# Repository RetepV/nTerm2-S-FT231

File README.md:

# nTerm2-S

> [!NOTE]
> This is the continuation of the design of the nTerm2-S (found here: https://github.com/RetepV/nTerm2-S). Now that I am reaching completion, I have decided to switch from using a CP2102 to using an FT231. The FT231 is just easier to solder with a soldering iron. Or better said: it CAN be soldered with a soldering iron, whereas with the CP2102 that's near impossible, it was a bad choice on my part.\
> \
> The version with the CP2102 will be 'archived', i.e. frozen. It really does work, you can build it if you like, it will run any FabGL code and example (except the MS-Dos emulator for lack of memory). But I will abandon it and continue developing on the FT231 version.

This is my rendition of the uTerm2-S by Just4Fun (https://hackaday.io/project/181583-uterm2-s-a-multi-emulation-color-rs232-terminal). My one is in SMD, and I hopefully made it easily hand-solderable for everyone. Obviously the 'n' in nTerm stands for 'nano.' :P

The nTerm2-S has a slightly more usable form than the uTerm2-S, I think. Smaller and more of a format of a useful tool. A "throw it in a drawer and grab it when you need it"- type of device. Taking little desk space and layed out for quick plugging and unplugging serial devices. For that I have also made it so that it can switch between normal and cross-cable (null-modem) from software, so that all you need is one cable and don't need extender boxes or a special null-modem cable.

It can also switch between hardware-supported RTS/CTS and DTR/DSR handshaking. With the sidenote that DTR/DSR are connected to RTS/CTS of the ESP32: the ESP32 does not have dedicated DSR/DTR signals in it's UART. It should work fine that way with old hardware, as the ESP32 is so fast that it will probably never have to deassert DTR (in reality RTS) anyway. And if the data set deasserts DSR, it means that the ESP32 will actually see CTS deasserted, and wait until CTS asserts again before continuing.

The nTerm2-S is ultimately based on the FABGL library and board design from Fabrizio Di Vittori. http://www.fabglib.org. However, I skipped Fabrizio's implementation and based my design on Just4Fun's uTerm2-S. https://j4f.info/uterm2-s

This board will run all FabGL software and examples, <ins>except</ins> the PC emulator. The PC emulator needs PSRAM, but the nTerm2-S does not have enough I/O pins left to connect a PSRAM. Maybe I will do a V2 at some point, using an I/O expander to free up ESP32 pins for connecting a PSRAM and an SD card. Or maybe I will make a new design using a newer version CPU. But let's finish the nTerm2-S first... ;)

# Software

For the software, please have a look here: https://github.com/RetepV/SporosTerm

All instructions for building the software from source are there. [But I also provide releases with handy scripts/batch files to easily program the board.](https://github.com/RetepV/SporosTerm/releases)

# Build instructions

I will provide build instructions here, when I actually have some. I'm going to build another one, and will make pictures.

# Progress

**27-2-2026**

Oops... I made a boo boo...

I have completely forgotten about the 5K1 resistors on the CC1 and CC2 lines of the USB-C connector. And hence, no USB-C device will provide power to the board, except some cheap and probably dangerous USB-C chargers. I knew I should have added them, I remember even making a mental note, but yet I never added them. How could this happen? Well, apart from simply my inexperience with USB, I have been testing all these months with a nice and long Nintendo USB cable, which has a USB-A on one end and a USB-C on the other. And I had it plugged into a USB hub, because I'd rather risk burning out the hub than a USB port on my laptop. But USB-A will happily provide power to anything, so my board always powered up fine. It was not until I wanted to change some settings in the FT231, and used a USB-C cable to directly connect it to my laptop, that I found the board didn't want to power up. Major facepalm. 🤦

Worst part (or better part, I'm not sure yet) is that this is quite a common mistake that people make. I should have know better, but on the other hand: it does make me feel a bit better that I'm not the only one. 😆

I quickly confirmed that this was the problem by wiring up the two resistors. And yep, now USB-C is giving the board power.

Adding two resistors seems like a quick and easy thing to do. But not this time, as the area where the resistors had to go was too crowded. So I had to refactor that whole area to make place. But now it looks a bit nicer too.

I also took the opportunity to update the graphics on the board. I moved some to the back and made them bigger (turns out that JLCPCB doesn't charge extra for solder mask on the back), added the URLs to these repositories, and add the FabGL and j4f repositories as well.

So here's v0.12. Only two resistors changed. Let's play a game of Spot the Differences:

This also has a consequence for the videos that I made. The videos are for a v0.11 board. What should I do? Make new boards yet again, and reshoot the videos? Maybe it's a good idea, because I learned a few things in the mean time, and the quality of the videos would become better. But the v0.11 videos are quite informational and educational already. I have to ponder this over a little.

By the way, I tallied up the costs of all the components. It comes down to about €40 for one board. But this was without looking for lower prices, I just went with the prices from Reichelt (https://www.reichelt.com).

[nTerm2-S FT231 BOM with prices.csv.zip](https://github.com/user-attachments/files/25616203/nTerm2-S.FT231.BOM.with.prices.csv.zip)

**26-2-2026**

I have been making videos while going from this:

To this:

I now have some video editing to do, which I have never done before in my life. Including adding a voiceover, because most of the time I was silent and concentrated during soldering. I did talk to myself in a few places, maybe I'll keep that. :)

A few mistakes were made, and I will show them uncensored. It resulted in a bunch of tips that are of general use when handsoldering SMD components. Let's see if I can make it educational. I hope that it will help some people take the plunge into SMD soldering. It's really not that hard. Just that you might need a 5x or 10x magnifying glass, like I do.

This is my fourth board (the other three were prototypes), and I was able to make it work in one go. When you watch the video, you'll see that I had a bit of jittery fingers, and that it caused me to make some mistakes. No shame in that!

**16-2-2026**

Just mentioning some progress here. I have started to build a new nTerm2-S, and am recording that. I have the handicap of not having great eyes anymore and have to solder using a magnifying glass these days. And this gets in the way of filming. So I had to rig something together. In the end I was able to ty my iPhone to the magnifying glass in such a way that I could look past it, while the iPhone looked straight down at my work area and my hands. That actually worked much better than I thought, except that if I accidentally touch the magnifying glass, the video wobbles a bit. :) Let's see if I can edit that out. No tricks, just honest handsoldering, including jittery hands, accidental baking of a resistor, and the occasional mistake that needed to be redone.

Anyway, here's a little unedited preview. Click it to play in Youtube.

**3-12-2025**

I found a little time to finally finish v0.11. This is it. I am not going to add anything more. Done deal. I will ask JLCPCB to fabricate a new set of v0.11 boards and will then build up one for the purpose of making pictures on how to solder one together. Maybe I'll make a video, which will be my first.

At the last possible moment, I added a 3-terminal pin header to optionally attach a 10K potmeter to, to use as volume control. I realised a bit late that if you build the amplifier and connect a speaker directly to the board, there is no way to control the volume. I can add volume control in software, but really: if you accidentally have the volume booming too loud, would you rather want to turn a volume pot or go into the setup menu, choose 'Audio', decrease the volume, and press Save? Anyway, it is optional and you can leave it out. Just don't forget to connect pins 1 and 2 on the 3-pin VOLUME header and solder R19. All info in the schematic.

I also improved some routing, and a few other little things.

**2-11-2025**

I have the Bluetooth working more or less great with Linux. I can pair, connect, disconnect, connect, disconnect, et

The problem of Macos, not properly being able to reconnect after a disconnect, seems to be a bug of Macos specifically. The Serial Port Profile (SPP) support on Macos is buggy. I have reported the bug with Apple, let's see wat happens.

**1-11-2025**

In between wrestling with trying to get the Bluetooth Serial Port Profile working and stable (which I am only moderately successful in, to be honest), I spent some time on a useless but fun thing: a signon screen. :)

About the Bluetooth SPP. It seems that I have it mostly under control now, it's quite usable and I'm not missing characters anymore. However, there is a problem that after pairing, it's only possible to connect one time. If we disconnect and try to connect again, the connection seems to be made, but no data is being transferred. If the nTerm2-S is 'forgotton' and paired again, it will work again for one connection only.

After browsing the internet, it seems that I am not the only one with this issue, and that it looks to be an issue with the ESP32's Bluetooth implementation loosing the pairing key for some reason.

There are some questions on the Espressif forums, and this one is quite detailed and seems to explain the issue quite well: https://esp32.com/viewtopic.php?p=151510&hilit=esp32+spp#p151510

**26-10-2025**

That newt had it coming, I swear!

@Fabrizio: it's really working well. Great job, thank you for all the work you did!

**26-10-2025**

I have been working on the software, and on testing. I don't have access to all types of hardware, but for now I have been testing with these:

* A Synertek SYM-1, which is the oldest computer that I currently own.
* An old(ish) Macbook (i7) running Ubuntu 24.04, with a serial dongle that is RS-232 V.24, i.e. uses -12V/+12V for communication.
* The latest version of the nTerm2-S, but without the audio and relay circuits (minimum configuration).
* A previous version of the nTerm2-S that I fully built for prototyping, and does have the audio and relay circuits.

I have been testing at different baud rates, and have been able to go all the way down to 110 baud successfully.

The SYM-1 doesn't go lower, so I thought to use my Linux machine to try `agetty` at 50 baud. But for some reason nothing under 110 baud would work. However, when I connect two nTerm2-S devices together, they can perfectly well communicate at 50 baud. So I suspect that the serial USB dongle has an issue with anything below 110 baud. I will have to check the signals with a scope to see what's really going on. The USB dongle uses a PL-2303 chip, and according to the datasheet it should be able to go down to at least 75 baud, and I suspect even lower. Maybe it's a driver issue.

On this latest prototype of the nTerm2-S, I did not populate the relay circuits. So to connect it to the Linux machine, I had to dig up a bunch of converters. And I had to quickly wire a null-modem converter too. So this reminded me again of why I added those relay circuits. They are worth it. :)

It IS actually a weird feeling to communicate with such a powerful Macbook over 110 baud. It really gave me the feeling that I was calling remotely into an old timesharing mainframe computer. :P

While testing with `agetty`, I found that I had forgotten to implement BRK functionality. So I quickly added that, and now I can ask `agetty` to cycle through a bunch of predetermined baud rates to match my nTerm2-S's baud rate.

Here's a picture of two nTerm2-S's connected to each other, where one has the relay circuits. No huge tree of converters, just one converter to go from DB25 to DB9, and then just set the Modem Type to 'Null modem' in the settings!

Another thing is the supported display resolution and display modes... Currently I offer 2 resolutions: 640x350 and 800x480. 800x480 is closest to the DEC VT340, which apparently was 800x500 pixels. At 800x480, there is just enough memory to have 8 colors (4 low and 4 high intensity). But it does give high resolution graphics, and it also gives a quite readable 132x25/50 characters (6 pixels wide characters).

At 640x350, I can have 16 colors. But what's more is, that if I use 640x350 monochrome, I can have the Bluetooth stack running! So it looks like I will support the following modes:

* 640x350, [80x24 + status bar, 80x25, 80x48 + status bar, 80x50], 2 colors, bluetooth
* 640x350, [80x24 + status bar, 80x25, 80x48 + status bar, 80x50], 16 colors, no bluetooth
* 800x480, [80x24 + status bar, 80x25, 80x48 + status bar, 80x50, 132x24 + status bar, 132x25, 132x48 + status bar, 132x50], 8 colors, no bluetooth

I do have a font that tries to show something readable when using 132x25 characters on a 640x350 resolution screen. It's not really something I take serious, but the font is there and is added quickly enough. Maybe it's worth it for some edge cases. Or just maybe, I could get a resolution of 800x350?

Higher resolutions than 800x480 are possible, but simply mean less colors because the ESP32 just does not have enough memory. There seems to be a solution for that, by adding PSRAM. But that would mean a hardware redesign, because there are no pins left to connect a PSRAM. I would have to add an I/O expander, either i2c or maybe 1-wire. That will only happen in a possible next version, which I will then probably also base on an ESP32-S3 (because it can do both UART and JTAG over USB, and is therefore tremendously much easier to debug).

I actually made a proof of concept already beginning of this year. But I will not build it (and it's not finished), as I really want to move on to the ESP32-S3 or maybe even something better.

https://github.com/RetepV/nTerm2-S-SD

**25-10-2025**

The last update was quite some time ago. I have been struggling with both time to work on this project, and struggling with the rendering issue of the terminal application. Somehow the glyph options of the Status Bar would sometimes 'bleed' over to the terminal text, causing letters to appear in reverse video. I had an inkling that this was being caused by the Status Bar rendering being interrupted by serial data being received and also rendered to the screen. Serial data is being received on an interrupt basis, so this was happening. However, I did not understand why.

It turns out that when we want to render a glyph on the Canvas, we use a function `drawText()`. But the glyph options (and foreground and background colors) are not passed together with the text. Instead, we use `setGlyphOptions`, `setPenColor` and `setBrushColor` to set up the parameters, and then call `drawText`, which will use the parameters that we set up. What the Canvas actually does with these calls is to post a message into a queue that will be read and processed by the DisplayController. This is necessary because the Canvas and the DisplayController code run on different cores and we need to take care of synchronising the messages: we cannot interrupt the DisplayController when we want, because that will lead to visible screen glitches. Using a queue is probably the easiest way to do this.

However, **both** the Canvas and the DisplayController keep their own version of those settings, i.e. there is more than one source of truth. The sources of truth are not updated at the same time, and that means that there is always a small amount of time where both will be out of sync. And this is the reason why sometimes the text received from the RS-232 was rendered with the `glyphOptions` of the Status Bar.

This is actually not so hard to fix. We just need to have only one source of truth, and pass the parameters together with the other relevant data (Glyph) through the queue. However, that would be a major fix, and actually a paradigm change. It could potentially have a lot of side effects, and I am not yet feeling up to handle that. Besides, it would be a backwards-compatibility breaking fix and so cannot be pushed back into Fabio's FabGL branch. And as I am only interested in the terminal emulation, I think I would better trip the FabGL library of all that is unnecessary and make a FabGLTerm or FabGLLite version or something. And I'm not sure if that is allowed by the license.

Anyway, another way to go is to leave everything as it is and simply **add** a `drawGlyph` command that takes `glyphOptions`, `penColor` and `brushColor`, and renders the glyph with the passed parameters instead of the (doubly) stored global `glyphOptions`, `penColor` and `brushColor`, call it `drawGlyphWithOptions`, and use that call to render the Status Bar. No sooner said than done, and the glitches disappeared. Success!

All the time that I was trying to work this out, I was wishing that I could connect a debugger to trace what was going on. But all the GPIO pins on the ESP32 are used for something, and there are no free pins to connect a JTAG debugger. This makes everything really hard to debug. If I make a next version of the nTerm2-S, I will choose for the ESP32 S3, which can do serial communications **and** JTAG over its USB port, making life so much easier.

Next steps are to clean up everything, reorganize the repository a bit, test with many more devices, and write some documentation. Possibly add a feature or two more.

What I have not mentioned before, is that I have also been busy implementing Bluetooth serial communications. The idea is that you can connect your PC to the Bluetooth UART and monitor what happens on the nTerm2-S. And more: you can send keystrokes to the nTerm2-S, which will forward it to the connected serial devices. The nTerm2-S is basically proxying between the serial device and the PC. The best part of this is that not only can you record the received serial data on the PC, but can also send data to the serial device, meaning that you can use the nTerm2-S to upload data. There are a few things to still iron out, but it's coming along quite nicely.

**23-6-2025**

Fixed a few small layout issues that I encountered while soldering, and then submitted as V0.10.

- Fixed orientation of C19.
- Changed orientations of R19 and C3. If you don't want the audio amplifier, you will still have to solder in the filter components R20, R21, C7 and C3. I placed C3 right under C7 now, and R19 (which does not need to be added) below that, making it more obvious what needs to be soldered and what not.
- Somehow the designation of C3 disappeared, I brought it back.
- Tweaked the positions of the connectors so that they are flush with the PCB edge. I should have done that earlier.
- Connected pins 2 and 3 of the CR2032 battery holder together. I didn't have the correct battery holder, so I soldered one in with a wire. I had to solder to pin 1 (-) and 3 (+) of the battery holder. But looking at the PCB, pin 2 is unconnected but also shows '+' in the solder mask. That's confusing, so I connected pin 2 to pin 3 so now both + pins can be used.

Here's the final result of v0.09. This is without the previously mentioned fixes, zoom in on the picture to find the issues. ;) 

I thought it might be nice to show the equipment that I use to solder nTerm2-S. This is it. Nothing more (ok, I also wear reading glasses).

- A lamp with 2x magnifying glass
- A small 10x magnifying loupe
- A steel set of quality pincers
- Edsyn FL-22 flux
- A Pinecil DC5525 soldering iron with ST-BC2 tip (the short variant of the BC2)
- 0.5mm 60/40 rosin-core solder
- A Goobay silicone soldering mat
- Forgot to picture: [a benchtop solder fume extractor](https://www.reichelt.com/nl/nl/shop/product/soldeerdamp-filtersysteem_zd-153_1m_min-90929?PROVID=2809&gad_source=1&gad_campaignid=22421704484&gclid=CjwKCAjw9uPCBhATEiwABHN9KxTfvpmQ8-ziKVJnDUi2Y7wfs4gk6s1T8yYnybVX92MnH0qx3_6JcRoCZEIQAvD_BwE), the most basic type

I also have a hot air station. But one of my goals is to make the nTerm2-S solderable without hot air, so I don't use it (I did need it for the CP2102, which is why I dropped that chip). I find that using hot air is not faster than hand soldering, possibly even slower. Hot air does have the benefit, though, that the components will align themselves automatically. The fastest way, however, will be to use solder paste with a stencil, and bake the PCB in an SMD oven. I don't have one, so hand soldering it is. ;)

And then software. Software is coming along quite well, but I have to iron out one quite major thing. The FabGL 'canvas' class works great if you only have one source of data. But I need to render the terminal text from serial input, but also the bottom status bar, so the canvas has 2 sources of data. Canvas, however, only has one set of text properties (bold, inverse, etc.). The serial input and status bar are sharing the text properties, and so I get some random inverse letters in the terminal text, when serial data is received while I'm in the middle of rendering the status bar. I really don't want to change FabGL much, but this is a fundamental problem of Canvas. It has only one render queue, and text properties are global to Canvas and are not properties of the drawText commands that are being put in the queue. There are some different options, but all seem hacky, and I have already kind of hacked the status bar into FabGL as it currently is. I might have to take a step back and change the strategy.

**22-6-2025**

Soldered the minimum configuration of the board for working as a SporosTerm, which means: everything except the relays and their control, and the audo amplifier. Technically, the LEDs and the RTC are not necessary either, but I consider them an indispensible part of the terminal. PCB is not cleaned of flux yet, so it looks dirty.

Connected everything and fired it up, and everything works. FabGL's Space Invaders, AnsiTerminal, Altair 8800 work. And SporosTerm works super too. The RTC works, it kept its time overnight. 

**21-6-2025**

Soldered R39 and R40, and the FT231 is recognized. The USB wants to give us 500mA, and on-board we have a perfect 3V3. The protection diodes work fine too.

Let's solder the ESP32, the reset circuitry and the power led. Then we can test if the ESP32 can be flashed.

Yep. Flashing works.

**20-6-2025**

Soldering commences, the FT231 solders really easily, that's a success! I did find one sloppyness on my side, C19 is rotated the wrong way. Of course it works just as fine in this orientation, but for sure people will accidentally solder it in the wrong way, as all the other C's are oriented the other way. That needs to be fixed in a V0.10, but it's cosmetic so no risk of breaking something.

Then life came in the way before I was able to solder R39 and R40, so I can't test yet.

**18-6-2025**

Received the new PCBs today. Won't be able to solder them as yet, other things have priority. :)

**12-6-2025**

I actually ordered 5 new boards from JLCPCB on 5-6-2025 (€15,99 including shipping). They were finished and shipped on 7-6-2025. Arrived in Leipzig (Germany) on 8-6-2025. They are taking their time and still have the package in their posession on 12-6-2025. So now waiting for them to pass it over to The Netherlands so that it can be delivered to me. What I learn from this is that the Chinese are very efficient, while the Germans seem to have lost their knack. I guess I shouldn't expect anything until end of next week.

Just before sending the board for manufacturing, I decided to add a few more solder bridges.

OPT1: Option to choose between using the on-board audi amplifier, or leave it out completely and have line-out.
OPT2-OPT5: Option to choose between having the null-modem switching option or not. If you don't want to use the null-modem option, you can leave out the relais and their control circuitry, and use the OPT2-OPT5 solder bridges to connect the UART directly to the RS-232 V24 connector. Note that this also removes the capability to switch between RTS/CTS and DTR/DSR.

So if you want to save a bit of money and don't want to use those subcomponents, you now can solder the bridges accordingly, instead of using a bypass bodge wire.

Ah, I also found out that the footprint for the VGA connector had been wrong all along. With both the prototypes, it was kind of hard to put the VGA connector pins in their holes. It turned out that the spacing was wrong. The connector would fit with a little bit of pushing, but that's not right. So I updated the footprint, and it should be good now.

**5-6-2025**

Three things progressed.

1. I decided to drop the supercap. I don't think it will last so long, they are meant to bridge short power downs, not long ones. I tested with a CR2032 and a BAT43 diode, and that works just as reliable as battery backup, but will give waaaaay more backup life.
2. I decided to add OPT2...OPT5 solder bridges to give people the options of leaving out the resistors and driver circuits. Soldering 1-2 on the solder bridges will make the signals go through the relay circuits, i.e. have software switchable RxD/TxD, RTS/CTS, or DTR/DSR. Soldering 2-3 will connect RxD, TxD, RTS and CTS directly to the RS-232 connector. It can save you some money if you don't need the switchability, and you can always change your mind later.
3. I also decided that This Is It. No more features, no more nothing, nTerm2-S is feature complete, and I am going to order new PCBs to see if everything actually still works. If everything works as planned, then I will consider nTerm2-S as being released. Software is hard on it's way. But if you can't wait, you can already use FabGL's AnsiTerminal example: the nTerm2-S hardware is backwards compatible.

The scary part is the FT-231 circuit. I have not tested it, and have to hope that I didn't make a mistake. The other more or less scary thing is that I had to move the AUDIO_PWM track, and hope that I did not introduce a bunch of crossover. The AUDIO_PWM track had to cross over the RxD_0 and TxD_0 lines. But these are only used for the ESP32 console ouput or during updating of the firmware. So if console output is removed, there should simply be nothing to cross over.

**29-5-2025**

The real time clock survived the night on only the backup power. :) At the last moment, I decided to put a series resistor of 150 ohm with the supercap (there was none in [Dallas's reference design](https://nl.mouser.com/datasheet/2/272/rtc-4-click-manual-v100-1483841.pdf). The inrush current when the supercap is empty of charge could be quite high. It's just for a short time, but theoretically it could cause such a power dip that it would cause boot loops. I haven't measured the inrush current, but "the word" is that it could even be multiple Amperes, which could theoretically also cause a track to burn.

I used a used Panasonic 1F 5.5V supercap that I had lying around, while I waiting for new ones to arrive.

I will also do some experiments with using a battery and an extra BAT43 diode. That's also 2 components, and maybe a better plan. If the voltage drop over the diode is too high, maybe I could use a NID5100?

**28-5-2025**

I just wanted to share some images of the progress I am making. I am still using the previous board with the CP2102 for developing and prototyping.

This is my development set up. I am testing with an actual computer, a Synertek SYM-1. It has 8K of ram, and runs Microsoft BASIC. Also note the tiny screen that I'm using. It's an old 800x480 LCD screen that I had laying around. I found out that it was LVDS, and purchased a board that can convert VGA (and HDMI and CVBS) to LVDS to drive the screen. Next thing is to make a case for it, but I couldn't wait to use it.

Closeup of the nTerm2-S and the screen.

Here I have added the DS2417 real time clock. It was easy, thanks to a whole bunch of people who created the [Arduino OneWire library](https://www.pjrc.com/teensy/td_libs_OneWire.html). I'm using a supercap as backup solution now, but might maybe switch to using a CR2023. But I'm not sure if that will work. I would have to add another diode in series making the voltage (in theory) 3V - 0.4V = 2.6V. But the lowest voltage supported by the DS2417 is 2.5V, so it's right on the edge. With the supercap I have some 3.2V. But the supercap will maybe last 2 weeks or so, while the CR2023 would probably last for years.

**23-5-2025**

What makes the difference between a home computer and a professional computer? The Real Time Clock! While working on the nTerm2-S firmware, I was able to add a status bar to the terminal. Memory is really tight, but CPU performance is not. So I thought: let's update it 10 times a second and show some sort of status of Rx, Tx, RTS and CTS, some blinkenlights. And then I thought that it would also be nice to show the time (and maybe date) in the status bar. That was quickly added. But well, what good are the time and date if you need to enter it manually every time you reset the terminal. So, we need an RTC.

Looking at the GPIO's left on the ESP32, there was a problem. Only one bidirectional GPIO (14) and one input-only (36) left. What can we do with that? I2C is out of the question, we need 1 output (or bidirectional) and 1 bidirectional GPIO for that. SPI even needs 3 GPIOs, and might possibly be done with only 2. But we have only 1 bidirectional wire... 1-wire! And looking around, I found the [Dallas Semiconductor DS2417](https://www.analog.com/media/en/technical-documentation/data-sheets/ds2417.pdf).

The DS2417 is not truly a real-time clock, but rather a 64-bit counter that is auto-incremented once a second, i.e. a timestamp. This is fine, in firmware we can convert it to a proper date and time with some functions. The counter can be battery backed-up. Perfect enough for a real-time clock. I will power it from a supercap, like in Dallas's design. Hopefully it will hold a charge for many months. If not, I might have to change the design again, to use a normal battery with a diode. First I'll build it on a breadboard to test it out somewhat.

The chip also has a kind of alarm function. Basically we can program it to give a /INT pulse after 1, 4, 32, 64, 2048, 4096, 65536, or 131072 seconds. Not of too much use, but as we also have one input-only GPIO left, we can connect the INT to it. Fortunately the input-only GPIO is GPIO14, which is one of the so-called RTC-GPIO and can be used to wake up the ESP32 from deep sleep. I don't have any idea for what we could use it. But it fills up the last unused GPIO pin, and it's a fitting for a complete feature-freeze and release of the hardware.

So said, so done (Dutch proverb). It was a bit of a tight squeeze because of the supercap battery's size. And I have always tried to make sure that the AUDIO_PWM is not close to any of the high-speed signals to prevent crosstalk (which would be hearable in the audio), so I had to lay that out differently as well. Hopefully crosstalk from the video into the audio track will still be next-to-nonexistent.

So now we are here:

# License

THIS IS A WORK IN PROGESS! I.E. UNLESS STATED AS WORKING, ASSUME THAT IT DOES NOT WORK! (but it's looking real good ;))

This design is available under GPL License V3. This means that I DO NOT release it for commercial use, unless with my explicit written and signed consent. Please contact me first if you have commercial questions.

uTerm2-S: https://hackaday.io/project/181583-uterm2-s-a-multi-emulation-color-rs232-terminal  
fabgl: http://www.fabglib.org/, https://github.com/fdivitto/FabGL

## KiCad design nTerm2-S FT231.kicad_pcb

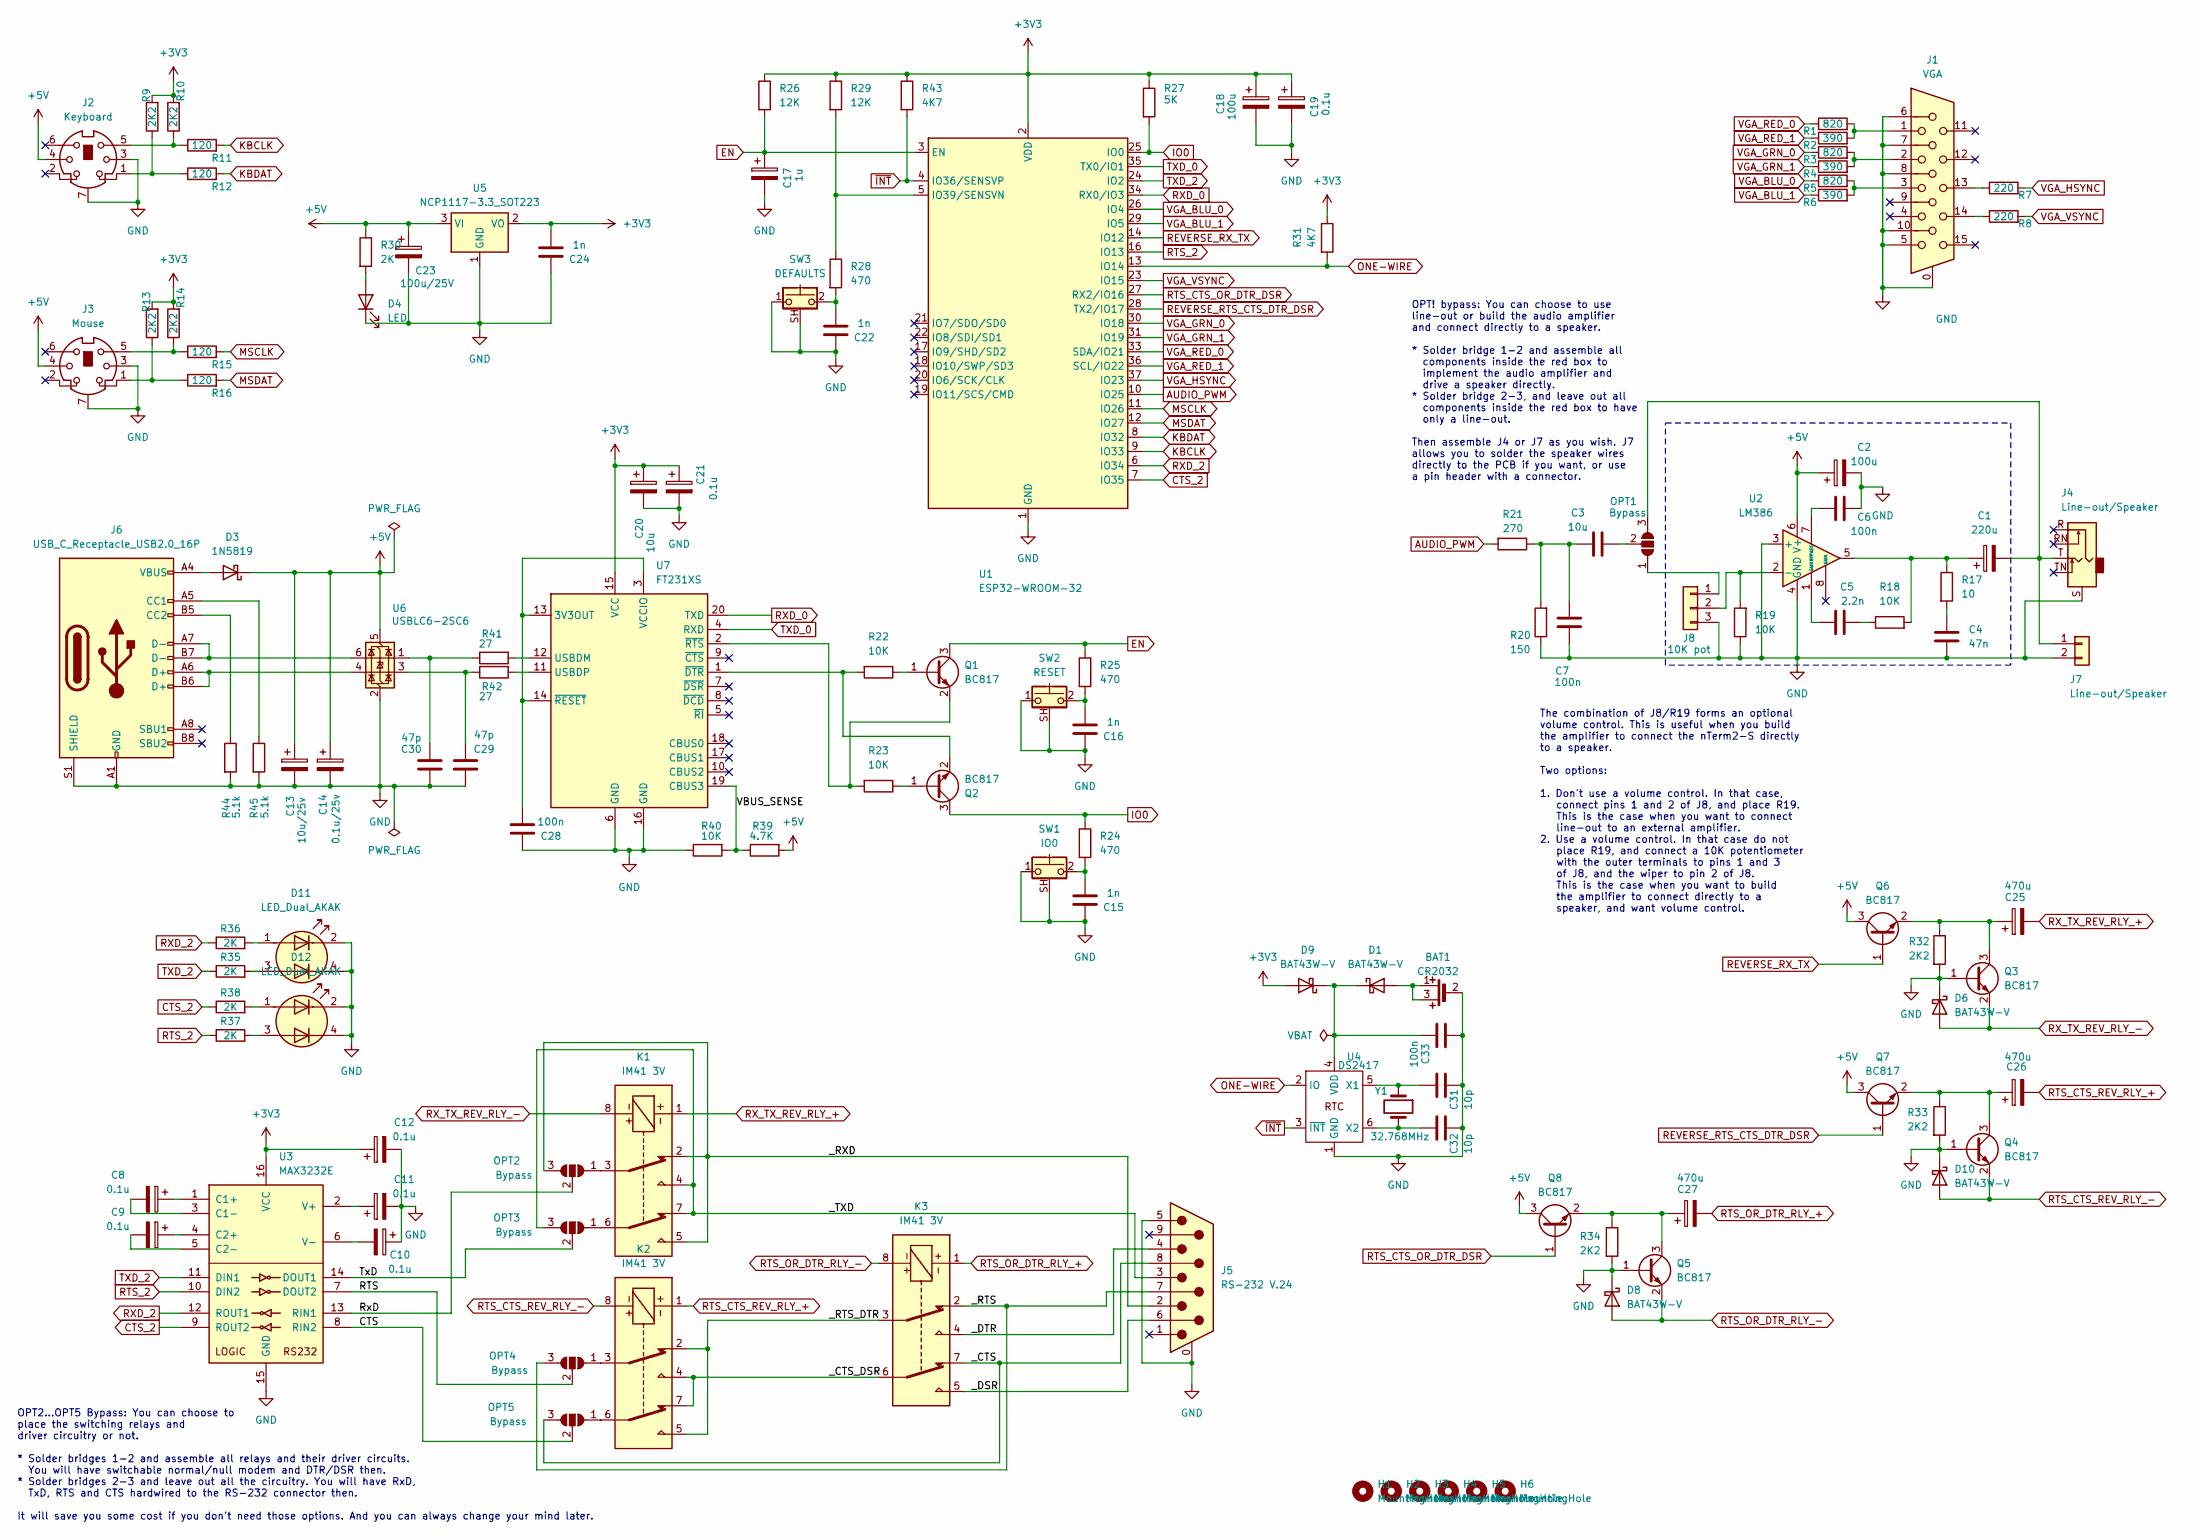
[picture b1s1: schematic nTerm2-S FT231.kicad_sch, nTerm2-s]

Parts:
BAT1: CR2032; TE Connectivity CR2032 V
C1: 220u; CP_Elec_6.3x7.7
C2: 100u; CP_Elec_5x5.4
C3: 10u; C_0805_2012Metric_Pad1.18x1.45mm_HandSolder
C4: 47n; C_0603_1608Metric_Pad1.08x0.95mm_HandSolder
C5: 2.2n; C_0603_1608Metric_Pad1.08x0.95mm_HandSolder
C6, C7, C28, C33: 100n; C_0603_1608Metric_Pad1.08x0.95mm_HandSolder
C8, C9, C10, C11, C12, C19, C21: 0.1u; CP_EIA-3216-18_Kemet-A_Pad1.58x1.35mm_HandSolder
C13: 10u/25v; CP_EIA-6032-28_Kemet-C_Pad2.25x2.35mm_HandSolder
C14: 0.1u/25v; CP_EIA-3216-18_Kemet-A_Pad1.58x1.35mm_HandSolder
C15, C16, C22, C24: 1n; C_0603_1608Metric_Pad1.08x0.95mm_HandSolder
C17: 1u; CP_EIA-3216-18_Kemet-A_Pad1.58x1.35mm_HandSolder
C18: 100u; CP_EIA-6032-28_Kemet-C_Pad2.25x2.35mm_HandSolder
C20: 10u; CP_EIA-3528-21_Kemet-B_Pad1.50x2.35mm_HandSolder
C23: 100u/25V; CP_EIA-7343-30_AVX-N_Pad2.25x2.55mm_HandSolder
C25, C26, C27: 470u; CP_Elec_6.3x7.7
C29, C30: 47p; C_0603_1608Metric_Pad1.08x0.95mm_HandSolder
C31, C32: 10p; C_0603_1608Metric_Pad1.08x0.95mm_HandSolder
D1, D6, D8, D9, D10: BAT43W-V; D_SOD-123
D3: 1N5819; Nexperia_CFP3_SOD-123W
D4: LED; DIALIGHT_LED_3MM_SINGLE
D11, D12: LED_Dual_AKAK; DIALIGHT_LED_3MM_DOUBLE
H1, H2, H3, H4, H5, H6: MountingHole; MountingHole_3.2mm_M3
J1: VGA; DSUB-15-HD AssMann HD 15FW
J2: Keyboard; Connector_Mini-DIN_Female_6Pin_2rows
J3: Mouse; Connector_Mini-DIN_Female_6Pin_2rows
J4: Line-out/Speaker; Jack_3.5mm_Ledino_KB3SPRS_Horizontal-alt
J5: RS-232 V.24; DSUB-9_Pins_Horizontal_P2.77x2.84mm_EdgePinOffset7.70mm_Hou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
J6: USB_C_Receptacle_USB2.0_16P; USB_C_Receptacle_Molex_213716-0001
J7: Line-out/Speaker; PinHeader_1x02_P2.54mm_Vertical
J8: 10K pot; PinHeader_1x03_P2.54mm_Vertical
K1, K2, K3: IM41 3V; Relay_DPDT_AXICOM_IMSeries_Gullwing
OPT1, OPT2, OPT3, OPT4, OPT5: Bypass; SolderJumper-3_P1.3mm_Open_RoundedPad1.0x1.5mm_NumberLabels
Q1, Q2, Q3, Q4, Q5, Q6, Q7, Q8: BC817; SOT-23
R1, R3, R5: 820; R_0603_1608Metric_Pad0.98x0.95mm_HandSolder
R2, R4, R6: 390; R_0603_1608Metric_Pad0.98x0.95mm_HandSolder
R7, R8: 220; R_0603_1608Metric_Pad0.98x0.95mm_HandSolder
R9, R10, R13, R14, R32, R33, R34: 2K2; R_0603_1608Metric_Pad0.98x0.95mm_HandSolder
R11, R12, R15, R16: 120; R_0603_1608Metric_Pad0.98x0.95mm_HandSolder
R17: 10; R_0603_1608Metric_Pad0.98x0.95mm_HandSolder
R18, R19, R22, R23, R40: 10K; R_0603_1608Metric_Pad0.98x0.95mm_HandSolder
R20: 150; R_0603_1608Metric_Pad0.98x0.95mm_HandSolder
R21: 270; R_0603_1608Metric_Pad0.98x0.95mm_HandSolder
R24, R25, R28: 470; R_0603_1608Metric_Pad0.98x0.95mm_HandSolder
R26, R29: 12K; R_0603_1608Metric_Pad0.98x0.95mm_HandSolder
R27: 5K; R_0603_1608Metric_Pad0.98x0.95mm_HandSolder
R30, R35, R36, R37, R38: 2K; R_0603_1608Metric_Pad0.98x0.95mm_HandSolder
R31, R43: 4K7; R_0603_1608Metric_Pad0.98x0.95mm_HandSolder
R39: 4.7K; R_0603_1608Metric_Pad0.98x0.95mm_HandSolder
R41, R42: 27; R_0603_1608Metric_Pad0.98x0.95mm_HandSolder
R44, R45: 5.1k; R_0603_1608Metric_Pad0.98x0.95mm_HandSolder
SW1: IO0; SW_Tactile_SPST_Angled_PTS645Vx58-2LFS-alt
SW2: RESET; SW_Tactile_SPST_Angled_PTS645Vx58-2LFS-alt
SW3: DEFAULTS; SW_Tactile_SPST_Angled_PTS645Vx58-2LFS-alt
U1: ESP32-WROOM-32
U2: LM386; SOIC-8_3.9x4.9mm_P1.27mm
U3: MAX3232E; SOIC-16_3.9x9.9mm_P1.27mm
U4: DS2417; TSOC-6_3.76x3.94mm_P1.27mm_handsolder
U5: NCP1117-3.3_SOT223; SOT-223-3_TabPin2
U6: USBLC6-2SC6; SOT-23-6
U7: FT231XS; SSOP-20_3.9x8.7mm_P0.635mm
Y1: 32.768MHz; Crystal_C38-LF_D3.0mm_L8.0mm_Horizontal

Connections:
+3V3: C12.1, C18.1, C19.1, C20.1, C21.1, C24.1, D9.2 (A), R9.2, R10.2, R13.2, R14.2, R26.1, R27.1, R29.1, R31.1, R43.1, U1.2 (VDD), U3.16 (VCC), U5.2 (VO), U7.15 (VCC)
+5V: C2.1, C13.1, C14.1, C23.1, D3.1 (K), J2.4, J3.4, Q6.3 (C), Q7.3 (C), Q8.3 (C), R30.1, R39.2, U2.6 (V+), U5.3 (VI), U6.5 (VBUS)
/CTS: OPT5.2 (C), U3.8 (RIN2)
/RTS: OPT4.2 (C), U3.7 (DOUT2)
/RxD: OPT2.2 (C), U3.13 (RIN1)
/TxD: OPT3.2 (C), U3.14 (DOUT1)
/VBUS_SENSE: R39.1, R40.2, U7.19 (CBUS3)
/_CTS: J5.8, K3.7, OPT5.3 (B)
/_CTS_DSR: K2.4, K2.7, K3.6
/_DSR: J5.6, K3.5
/_DTR: J5.4, K3.4
/_RTS: J5.7, K3.2, OPT4.3 (B)
/_RTS_DTR: K2.2, K2.5, K3.3
/_RXD: J5.2, K1.2, K1.5, OPT2.3 (B)
/_TXD: J5.3, K1.4, K1.7, OPT3.3 (B)
AUDIO_PWM: R21.2, U1.10 (IO25)
CTS_2: R38.1, U1.7 (IO35), U3.9 (ROUT2)
EN: C17.1, Q1.3 (C), R25.1, R26.2, U1.3 (EN)
GND: BAT1.2, C2.2, C4.2, C6.2, C7.1, C10.1, C11.2, C12.2, C13.2, C14.2, C15.2, C16.2, C17.2, C18.2, C19.2, C20.2, C21.2, C22.2, C23.2, C24.2, C28.2, C29.2, C30.2, C31.2, C32.2, C33.2, D4.2 (K), D6.1 (K), D8.1 (K), D10.1 (K), D11.2 (K1), D11.4 (K2), D12.2 (K1), D12.4 (K2), J1.0, J1.5, J1.6, J1.7, J1.8, J1.10, J2.3, J2.7, J3.3, J3.7, J4.S, J5.0 (PAD), J5.5, J6.A1 (GND), J6.A12 (GND), J6.B1 (GND), J6.B12 (GND), J6.S1 (SHIELD), J7.2, J8.3, Q3.1 (B), Q4.1 (B), Q5.1 (B), R19.1, R20.1, R32.2, R33.2, R34.2, R40.1, R44.2, R45.2, SW1.1, SW1.SH (B), SW2.1, SW2.SH (B), SW3.1, SW3.SH (B), U1.1 (GND), U1.15 (GND), U1.38 (GND), U1.39 (GND), U2.3 (+), U2.4 (GND), U3.15 (GND), U4.1 (GND), U5.1 (GND), U6.2 (GND), U7.6 (GND), U7.16 (GND)
IO0: Q2.3 (C), R24.1, R27.2, U1.25 (IO0)
KBCLK: R11.2, U1.9 (IO33)
KBDAT: R12.2, U1.8 (IO32)
MSCLK: R15.2, U1.11 (IO26)
MSDAT: R16.2, U1.12 (IO27)
unnamed: C1.1, R17.1, R18.2, U2.5
unnamed: C3.1, C7.2, R20.2, R21.1
unnamed: C4.1, R17.2
unnamed: C5.1, U2.1 (GAIN)
unnamed: C5.2, R18.1
unnamed: C15.1, R24.2, SW1.2
unnamed: C16.1, R25.2, SW2.2
unnamed: C22.1, R28.2, SW3.2
unnamed: C29.1, R42.1, U6.3 (I/O2)
unnamed: C30.1, R41.1, U6.1 (I/O1)
unnamed: BAT1.1, BAT1.3, D1.2 (A)
unnamed: C33.1, D1.1 (K), D9.1 (K), U4.4 (VDD)
unnamed: D3.2 (A), J6.A4 (VBUS), J6.A9 (VBUS), J6.B4 (VBUS), J6.B9 (VBUS)
unnamed: D4.1 (A), R30.2
unnamed: D11.1 (A1), R36.2
unnamed: D11.3 (A2), R35.2
unnamed: D12.1 (A1), R38.2
unnamed: D12.3 (A2), R37.2
unnamed: J1.1, R1.2, R2.2
unnamed: J1.2, R3.2, R4.2
unnamed: J1.3, R5.2, R6.2
unnamed: J1.13, R7.1
unnamed: J1.14, R8.1
unnamed: J2.1, R9.1, R12.1
unnamed: J2.5, R10.1, R11.1
unnamed: J3.1, R13.1, R16.1
unnamed: J3.5, R14.1, R15.1
unnamed: J6.A5 (CC1), R45.1
unnamed: J6.B5 (CC2), R44.1
unnamed: J6.A6 (D+), J6.B6 (D+), U6.4 (I/O2)
unnamed: J6.A7 (D-), J6.B7 (D-), U6.6 (I/O1)
unnamed: C1.2, J4.T, J7.1, OPT1.3 (B)
unnamed: J8.1, OPT1.1 (A)
unnamed: J8.2, R19.2, U2.2 (-)
unnamed: C3.2, OPT1.2 (C)
unnamed: K1.3, OPT2.1 (A)
unnamed: K1.6, OPT3.1 (A)
unnamed: K2.3, OPT4.1 (A)
unnamed: K2.6, OPT5.1 (A)
unnamed: Q1.1 (B), R22.1
unnamed: Q1.2 (E), R23.2, U7.2 (~RTS)
unnamed: Q2.1 (B), R23.1
unnamed: Q2.2 (E), R22.2, U7.1 (~DTR)
unnamed: C25.1, Q3.3 (C), Q6.2 (E), R32.1
unnamed: C26.1, Q4.3 (C), Q7.2 (E), R33.1
unnamed: C27.1, Q5.3 (C), Q8.2 (E), R34.1
unnamed: R28.1, R29.2, U1.5 (IO39/SENSVN)
unnamed: C6.1, U2.7 (BYPASS)
unnamed: C8.1, U3.1 (C1+)
unnamed: C8.2, U3.3 (C1-)
unnamed: C9.1, U3.4 (C2+)
unnamed: C9.2, U3.5 (C2-)
unnamed: C11.1, U3.2 (V+)
unnamed: C10.2, U3.6 (V-)
unnamed: C31.1, U4.5 (X1), Y1.1
unnamed: C32.1, U4.6 (X2), Y1.2
unnamed: C28.1, U7.3 (VCCIO), U7.13 (3V3OUT), U7.14 (~RESET)
unnamed: R41.2, U7.12 (USBDM)
unnamed: R42.2, U7.11 (USBDP)
ONE-WIRE: R31.2, U1.13 (IO14), U4.2 (IO)
REVERSE_RTS_CTS_DTR_DSR: Q7.1 (B), U1.28 (TX2/IO17)
REVERSE_RX_TX: Q6.1 (B), U1.14 (IO12)
RTS_2: R37.1, U1.16 (IO13), U3.10 (DIN2)
RTS_CTS_OR_DTR_DSR: Q8.1 (B), U1.27 (RX2/IO16)
RTS_CTS_REV_RLY_+: C26.2, K2.1
RTS_CTS_REV_RLY_-: D10.2 (A), K2.8, Q4.2 (E)
RTS_OR_DTR_RLY_+: C27.2, K3.1
RTS_OR_DTR_RLY_-: D8.2 (A), K3.8, Q5.2 (E)
RXD_0: U1.34 (RX0/IO3), U7.20 (TXD)
RXD_2: R36.1, U1.6 (IO34), U3.12 (ROUT1)
RX_TX_REV_RLY_+: C25.2, K1.1
RX_TX_REV_RLY_-: D6.2 (A), K1.8, Q3.2 (E)
TXD_0: U1.35 (TX0/IO1), U7.4 (RXD)
TXD_2: R35.1, U1.24 (IO2), U3.11 (DIN1)
VGA_BLU_0: R5.1, U1.26 (IO4)
VGA_BLU_1: R6.1, U1.29 (IO5)
VGA_GRN_0: R3.1, U1.30 (IO18)
VGA_GRN_1: R4.1, U1.31 (IO19)
VGA_HSYNC: R7.2, U1.37 (IO23)
VGA_RED_0: R1.1, U1.33 (SDA/IO21)
VGA_RED_1: R2.1, U1.36 (SCL/IO22)
VGA_VSYNC: R8.2, U1.23 (IO15)
~INT: R43.2, U1.4 (IO36/SENSVP), U4.3 (~INT)

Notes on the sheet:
OPT2...OPT5 Bypass: You can choose to place the switching relays and driver circuitry or not. * Solder bridges 1-2 and assemble all relays and their driver circuits. You will have switchable normal/null modem and DTR/DSR then. * Solder bridges 2-3 and leave out all the circuitry. You will have RxD,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
The combination of J8/R19 forms an optional volume control. This is useful when you build the amplifier to connect the nTerm2-S directly to a speaker. Two options: 1. Don't use a volume control. In that case, connect pins 1 and 2 of J8, and place R19. This is the case when you want to connect line-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
OPT! bypass: You can choose to use line-out or build the audio amplifier and connect directly to a speaker. * Solder bridge 1-2 and assemble all components inside the red box to implement the audio amplifier and drive a speaker directly. * Solder bridge 2-3, and leave out all components inside the 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

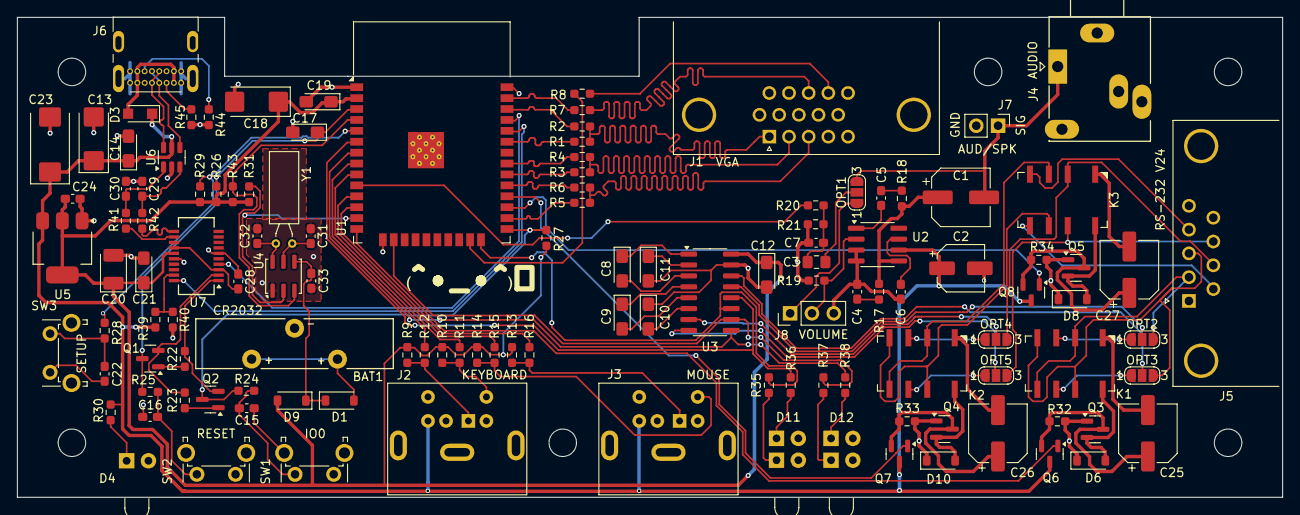
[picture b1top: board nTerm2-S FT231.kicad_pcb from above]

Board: 2 copper layers, 147.3 x 55.9 mm, 129 parts (0 on the bottom side), 107 nets.

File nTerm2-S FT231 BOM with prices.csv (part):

Id,Designator,Footprint,Quantity,Designation,Supplier and ref,Price €,Total €,Notes
1,"R28,R25,R24",R_0603_1608Metric_Pad0.98x0.95mm_HandSolder,3,470,https://www.reichelt.com/nl/en/shop/product/smd_chip_resisto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,"0,02","0,06",
2,"R2,R4,R6",R_0603_1608Metric_Pad0.98x0.95mm_HandSolder,3,390,https://www.reichelt.com/nl/en/shop/product/smd_chip_resisto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,"0,02","0,06",
3,"R26,R29",R_0603_1608Metric_Pad0.98x0.95mm_HandSolder,2,12K,https://www.reichelt.com/nl/en/shop/product/smd_chip_resisto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,"0,02","0,04",
4,"R33,R14,R34,R32,R9,R13,R10",R_0603_1608Metric_Pad0.98x0.95mm_HandSolder,7,2K2,https://www.reichelt.com/nl/en/shop/product/smd_chip_resisto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,"0,02","0,14",
5,"R41,R42",R_0603_1608Metric_Pad0.98x0.95mm_HandSolder,2,27,https://www.reichelt.com/nl/en/shop/product/smd_chip_resisto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,"0,02","0,04",
6,U4,TSOC-6_3.76x3.94mm_P1.27mm,1,DS2417,https://www.digikey.nl/en/products/detail/analog-devices-inc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,"3,87","3,87","Shop around, you can find them cheaper."
7,"R18,R40,R22,R23,R19",R_0603_1608Metric_Pad0.98x0.95mm_HandSolder,5,10K,https://www.reichelt.com/nl/en/shop/product/smd_chip_resisto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,"0,02","0,1",
8,"D10,D9,D6,D8,D1",D_SOD-123,5,BAT43W-V,https://www.reichelt.com/nl/en/shop/product/schottky_diode_3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,"0,05","0,25",
9,"K1,K2,K3",Relay_DPDT_AXICOM_IMSeries_Gullwing,3,IM41 3V,https://www.reichelt.com/nl/en/shop/product/axicom_im_signal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,"1,88","5,64","Shop around, you can find them cheaper, maybe from other manufacturers."
10,SW2,SW_Tactile_SPST_Angled_PTS645Vx58-2LFS-alt,1,RESET,https://www.reichelt.com/nl/en/shop/product/short-stroke_key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,"0,2","0,2",
11,J7,PinHeader_1x02_P2.54mm_Vertical,1,Line-out/Speaker,https://www.reichelt.com/nl/en/shop/product/pin_header_1x2_p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,"0,02","0,02",Don’t buy this. Buy a strip and break off 2 pins.
12,R17,R_0603_1608Metric_Pad0.98x0.95mm_HandSolder,1,10,https://www.reichelt.com/nl/en/shop/product/smd_chip_resisto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,"0,02","0,02",
13,U1,ESP32-WROOM-32,1,ESP32-WROOM-32,https://www.reichelt.com/nl/en/shop/product/wifi_smd_module_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,"4,22","4,22",
14,SW1,SW_Tactile_SPST_Angled_PTS645Vx58-2LFS-alt,1,IO0,https://www.reichelt.com/nl/en/shop/product/short-stroke_key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,"0,2","0,2",
15,"C6,C33,C7,C28",C_0603_1608Metric_Pad1.08x0.95mm_HandSolder,4,100n,https://www.reichelt.com/nl/en/shop/product/smd_multilayer_0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,"0,02","0,08",
16,J2,Connector_Mini-DIN_Female_6Pin_2rows,1,Keyboard,https://www.reichelt.com/nl/en/shop/product/6-pin_mini-din_s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,"1,12","1,12",
17,"C25,C26,C27",CP_Elec_6.3x7.7,3,470u,https://www.reichelt.com/nl/en/shop/product/electrolytic_cap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,"0,25","0,75",
18,"C30,C29",C_0603_1608Metric_Pad1.08x0.95mm_HandSolder,2,47p,https://www.reichelt.com/nl/en/shop/product/multi-layer_cera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,"0,02","0,04",
19,"D11,D12",DIALIGHT_LED_3MM_DOUBLE,2,LED_Dual_AKAK,https://www.reichelt.com/nl/en/shop/product/led_module_red_g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,"2,54","5,08","Shop around, you can find them cheaper"
20,"R38,R37,R36,R35,R30",R_0603_1608Metric_Pad0.98x0.95mm_HandSolder,5,2K,https://www.reichelt.com/nl/en/shop/product/smd_chip_resisto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,"0,14","0,7","Should be able to get them for 0,02 cents"
21,U2,SOIC-8_3.9x4.9mm_P1.27mm,1,LM386,https://www.reichelt.com/nl/en/shop/product/audio_amplifier_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,"0,37","0,37",
22,"R8,R7",R_0603_1608Metric_Pad0.98x0.95mm_HandSolder,2,220,https://www.reichelt.com/nl/en/shop/product/smd_chip_resisto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,"0,02","0,04",
23,"C24,C16,C15,C22",C_0603_1608Metric_Pad1.08x0.95mm_HandSolder,4,1n,https://www.reichelt.com/nl/en/shop/product/smd_multilayer_0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,"0,02","0,08",
24,"R12,R15,R16,R11",R_0603_1608Metric_Pad0.98x0.95mm_HandSolder,4,120,https://www.reichelt.com/nl/en/shop/product/smd_chip_resisto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,"0,02","0,08",
25,"C10,C9,C21,C12,C8,C11,C19",CP_EIA-3216-18_Kemet-A_Pad1.58x1.35mm_HandSolder,7,0.1u,https://www.reichelt.com/nl/en/shop/product/smd-tantalum_100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,"0,25","1,75",
26,C14,CP_EIA-3216-18_Kemet-A_Pad1.58x1.35mm_HandSolder,1,0.1u/25v,https://www.reichelt.com/nl/en/shop/product/smd-tantalum_100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,"0,25","0,25",
27,J3,Connector_Mini-DIN_Female_6Pin_2rows,1,Mouse,https://www.reichelt.com/nl/en/shop/product/6-pin_mini-din_s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,"1,01","1,01",
28,U5,SOT-223-3_TabPin2,1,NCP1117-3.3_SOT223,https://www.reichelt.com/nl/en/shop/product/ldo_controller_f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,"0,3","0,3",
29,C18,CP_EIA-6032-28_Kemet-C_Pad2.25x2.35mm_HandSolder,1,100u,https://www.reichelt.com/nl/en/shop/product/smd-tantalum_100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,"0,46","0,46",
30,"C31,C32",C_0603_1608Metric_Pad1.08x0.95mm_HandSolder,2,10p,https://www.reichelt.com/nl/en/shop/product/smd_multilayer_0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,"0,02","0,04",
31,R20,R_0603_1608Metric_Pad0.98x0.95mm_HandSolder,1,150,https://www.reichelt.com/nl/en/shop/product/smd_chip_resisto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,"0,02","0,02",
32,U3,SOIC-16_3.9x9.9mm_P1.27mm,1,MAX3232E,https://www.reichelt.com/nl/en/shop/product/rs232_2_drivers_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,"2,49","2,49",
33,C23,CP_EIA-7343-30_AVX-N_Pad2.25x2.55mm_HandSolder,1,100u/25V,https://www.reichelt.com/nl/en/shop/product/smd-tantal_capac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,"2,02","2,02",
34,"Q5,Q6,Q2,Q7,Q1,Q3,Q8,Q4",SOT-23,8,BC817,https://www.reichelt.com/nl/en/shop/product/bipolar_transist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,"0,03","0,24",
35,J6,USB_C_Receptacle_Molex_213716-0001,1,USB_C_Receptacle_USB2.0_16P,https://nl.farnell.com/molex/213716-0001/usb-conn-2-0-type-c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,"1,31","1,31","Is a bit hard to find. Possibly you could substitute it with GCT USB4085, but it does look to have a bit different measurements. https://www.digikey.com/en/products/detail/gct/USB4085-GF-A/9859733"
36,"R31,R43",R_0603_1608Metric_Pad0.98x0.95mm_HandSolder,2,4K7,https://www.reichelt.com/nl/en/shop/product/smd_chip_resisto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,"0,02","0,04",
37,C20,CP_EIA-3528-21_Kemet-B_Pad1.50x2.35mm_HandSolder,1,10u,https://www.reichelt.com/nl/en/shop/product/smd-tantalum_10_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,"0,22","0,22",
38,SW3,SW_Tactile_SPST_Angled_PTS645Vx58-2LFS-alt,1,DEFAULTS,https://www.reichelt.com/nl/en/shop/product/short-stroke_key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,"0,2","0,2",
39,R39,R_0603_1608Metric_Pad0.98x0.95mm_HandSolder,1,4.7K,https://www.reichelt.com/nl/en/shop/product/smd_chip_resisto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,"0,02","0,02",
40,C5,C_0603_1608Metric_Pad1.08x0.95mm_HandSolder,1,2.2n,https://www.reichelt.com/nl/en/shop/product/smd_multilayer_c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,"0,02","0,02",
41,"R5,R3,R1",R_0603_1608Metric_Pad0.98x0.95mm_HandSolder,3,820,https://www.reichelt.com/nl/en/shop/product/smd_chip_resisto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,"0,02","0,06",
42,BAT1,TE Connectivity CR2032 V,1,CR2032,https://www.reichelt.com/nl/en/shop/product/button_cell_hold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,"0,84","0,84",Others may fit
43,D4,DIALIGHT_LED_3MM_SINGLE,1,LED,https://www.reichelt.com/nl/en/shop/search/dialight%203mm?GR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,"0,97","0,97",
44,U6,SOT-23-6,1,USBLC6-2SC6,https://www.reichelt.com/nl/en/shop/product/esd_protection_d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,"0,15","0,15",
45,J5,DSUB-9_Pins_Horizontal_P2.77x2.84mm_EdgePinOffset7.70mm_Housed_MountingHolesOffset9.12mm,1,RS-232 V.24,https://www.reichelt.com/nl/en/shop/product/d-sub-jack_9-pol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,"0,33","0,33",
46,C2,CP_Elec_5x5.4,1,100u,https://www.reichelt.com/nl/en/shop/product/smd-e-cap_radial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,"0,22","0,22",
47,C1,CP_Elec_6.3x7.7,1,220u,https://www.reichelt.com/nl/en/shop/product/smd-capacitor_22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,"0,2","0,2",
48,J1,DSUB-15-HD AssMann HD 15FW,1,VGA,https://www.reichelt.com/nl/en/shop/product/d-sub_socket_hig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,"0,43","0,43",
49,R21,R_0603_1608Metric_Pad0.98x0.95mm_HandSolder,1,270,https://www.reichelt.com/nl/en/shop/product/smd_chip_resisto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,"0,02","0,02",
50,J8,PinHeader_1x03_P2.54mm_Vertical,1,10K pot,https://www.reichelt.com/nl/en/shop/product/pin_header_1_x_3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,"0,1","0,1",Don’t buy this. Buy a strip and break off 3 pins.
51,C3,C_0805_2012Metric_Pad1.18x1.45mm_HandSolder,1,10u,https://www.reichelt.com/nl/en/shop/product/mlcc_0603_10_uf_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,"0,03","0,03","I have made a mistake here, it should have been size 0603 and not 0805. You can use either if you want, they will both fit. But I just used the 0603."
52,J4,Jack_3.5mm_Ledino_KB3SPRS_Horizontal-alt,1,Line-out/Speaker,https://www.reichelt.com/nl/en/shop/product/jack_socket_3_5_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,"0,37","0,37",
53,C4,C_0603_1608Metric_Pad1.08x0.95mm_HandSolder,1,47n,https://www.reichelt.com/nl/en/shop/product/multi-layer_cera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,"0,02","0,02",
54,Y1,Crystal_C38-LF_D3.0mm_L8.0mm_Horizontal,1,32.768KHz,https://www.reichelt.com/nl/en/shop/product/quartz_32_768_kh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,"0,25","0,25",
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
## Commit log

2025-05-21 Initial commit of nTerm2-S with an FT231 instead of a CP2102. I have also added an RTC.
2025-05-21 Add JPEG and PDFs
2025-05-21 Exported library and footprints to project local library for distribution.
2025-05-30 Changed supercap to a CR2032 battery for timekeeping. Exported library. Fixed VGA footprint. Added a few more 3D footprints.
2025-05-30 Update revision to 0.7.
2025-06-05 And here's revision 0.08. I added some solder bridges so that people can choose to place the relays and driver circuits, or forego on the switching option and just be happy with RxD, TxD, RTS and CTS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
2025-06-05 Ah, oops, forgot to update the release number in the PCB info text. :)
2025-06-05 Generate gerbers and drill files for revision 0.08.
2025-06-06 Zipped production files. These are the files that were submitted to JLPCB for the production of v0.08.
2025-06-06 Add thermal reliefs to C31 and C32. Bump revision to 0.09.
2025-06-06 Commit some backups.
2025-06-23 V0.10 small detail fixes. - Rotate C19 180 degrees, so that it's oriented as the rest of the caps. - Tweak the positions of several connectors and LEDs so that they are flush with the PCB edge. - Con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
2025-06-23 V0.10: somehow the reference of C3 disappeared. Made it reappear. No need to update the version number for this.
2025-06-23 Archive gerbers for v0.09, generate gerbers for v0.10.
2025-10-25 Update README with progress and rendering issue details
    Added detailed progress update on rendering issues and debugging challenges faced with the terminal application. Discussed potential solutions and future plans for the nTerm2-S project.
2025-10-25 Update README with next steps and Bluetooth details
    Outline next steps and Bluetooth feature implementation.
2025-10-26 Update README with progress and testing details
    Added detailed progress update on software testing and display modes for nTerm2-S project.
2025-10-26 Revise display modes and resolutions in README
    Updated display modes and resolutions section with detailed options.
2025-10-26 Update README with PSRAM and hardware redesign details
    Clarified future hardware redesign plans for higher resolutions.
2025-10-26 Update README with baud rate testing and display modes
    Added details about testing baud rates, relay circuits, and display modes. Updated information on resolutions and memory considerations for the ESP32. Added some pictures.
2025-10-26 Update README with nTerm2-S connection details
    Clarified the converter setup for nTerm2-S connections and added details about display resolutions.
2025-10-26 Format dates in bold and refine text
    Updated dates to bold formatting and made minor text adjustments for clarity.
2025-10-26 Fix grammatical error in display resolution description
    Corrected the phrasing from 'are supported' to 'is supported' in the display resolution section.
2025-10-26 Update README with proof of concept details
    Added a note about a proof of concept for PSRAM and future plans.
2025-10-26 Update README with progress and hardware details
    Added a personal note and updated hardware testing details.
2025-10-28 Add software section and build instructions note
    Added software section with link to SporosTerm repository and build instructions note.
2025-11-01 Update README with progress on Bluetooth SPP and UI
    Added progress updates related to Bluetooth SPP and signon screen.
2025-11-02 Update README with Bluetooth progress and MacOS bug report
    Added progress update regarding Bluetooth functionality on Linux and MacOS issues.
2025-12-03 nTerm2-S V0.11
    * Added a footprint for a volume control potmeter.
    * Improved routing around R29, R26, R43 and R31. It's not super still, but better than routing 2 traces under a resistor.
    * New documentation, including a proper render that will help with placing components.
    * Added bunch of 3D packages
    * Resolved some library issues
    * Created fabrication files for v0.11
2025-12-03 Let's add this backup too, which Kicad just created.
2025-12-03 Document v0.11 completion and volume control feature
    Added final updates and details for v0.11, including volume control options and improvements.
2025-12-03 Add cinematic render
2026-01-14 Update README with clearer build instructions
    Clarified instructions for building the software from source and programming the board.
2026-01-14 Add link to releases for programming scripts
    Updated the README to include a link to the releases page for easier access to scripts and batch files.
2026-02-15 Update README with project progress and v0.11 details
    Added updates on progress with nTerm2-S project and v0.11 completion details.
2026-02-15 Update progress date and project details in README
    Updated progress date and added details about the new nTerm2-S build process.
2026-02-26 Update README with progress and video editing notes
    Added progress updates and personal insights on video editing and soldering techniques.
2026-02-26 Update README with personal soldering experiences
    Added personal insights and experiences related to SMD soldering and video recording.
2026-02-27 Big booboo! I forgot about the 5K1 resistors necessary on the CC lines of the USB-C connector. With those, the USB-C will not give power to the board. If you use a USB-A to USB-C cable, it works grea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
2026-02-27 Document USB-C power issue and board updates
    Added a detailed explanation regarding the omission of 5K1 resistors on the USB-C connector and the impact on board power. Updated the version to v0.12 and mentioned changes made to the board graphic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
2026-02-27 Revise README for v0.12 updates and graphics
    Updated README to reflect changes in v0.12, including graphics updates and a new image.
2026-02-27 Update README with component costs and BOM link
    Added component cost details and a BOM file link.
2026-03-02 Update BOM with some alternatives for the IM41GR relays. The relays are the most expensive parts on the BOM, and there is some money to be saved by searching for alternatives from different manufactu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
2026-03-02 Update BOM with some alternatives for the IM41GR relay.

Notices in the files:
nTerm2-S FT231.kicad_pcb:
© 2025, 2026 Sporos Tech ₍^•_•^₎ﾉ, Peter de Vroomen
© 2025, 2026 Sporos Tech, Peter de Vroomen
